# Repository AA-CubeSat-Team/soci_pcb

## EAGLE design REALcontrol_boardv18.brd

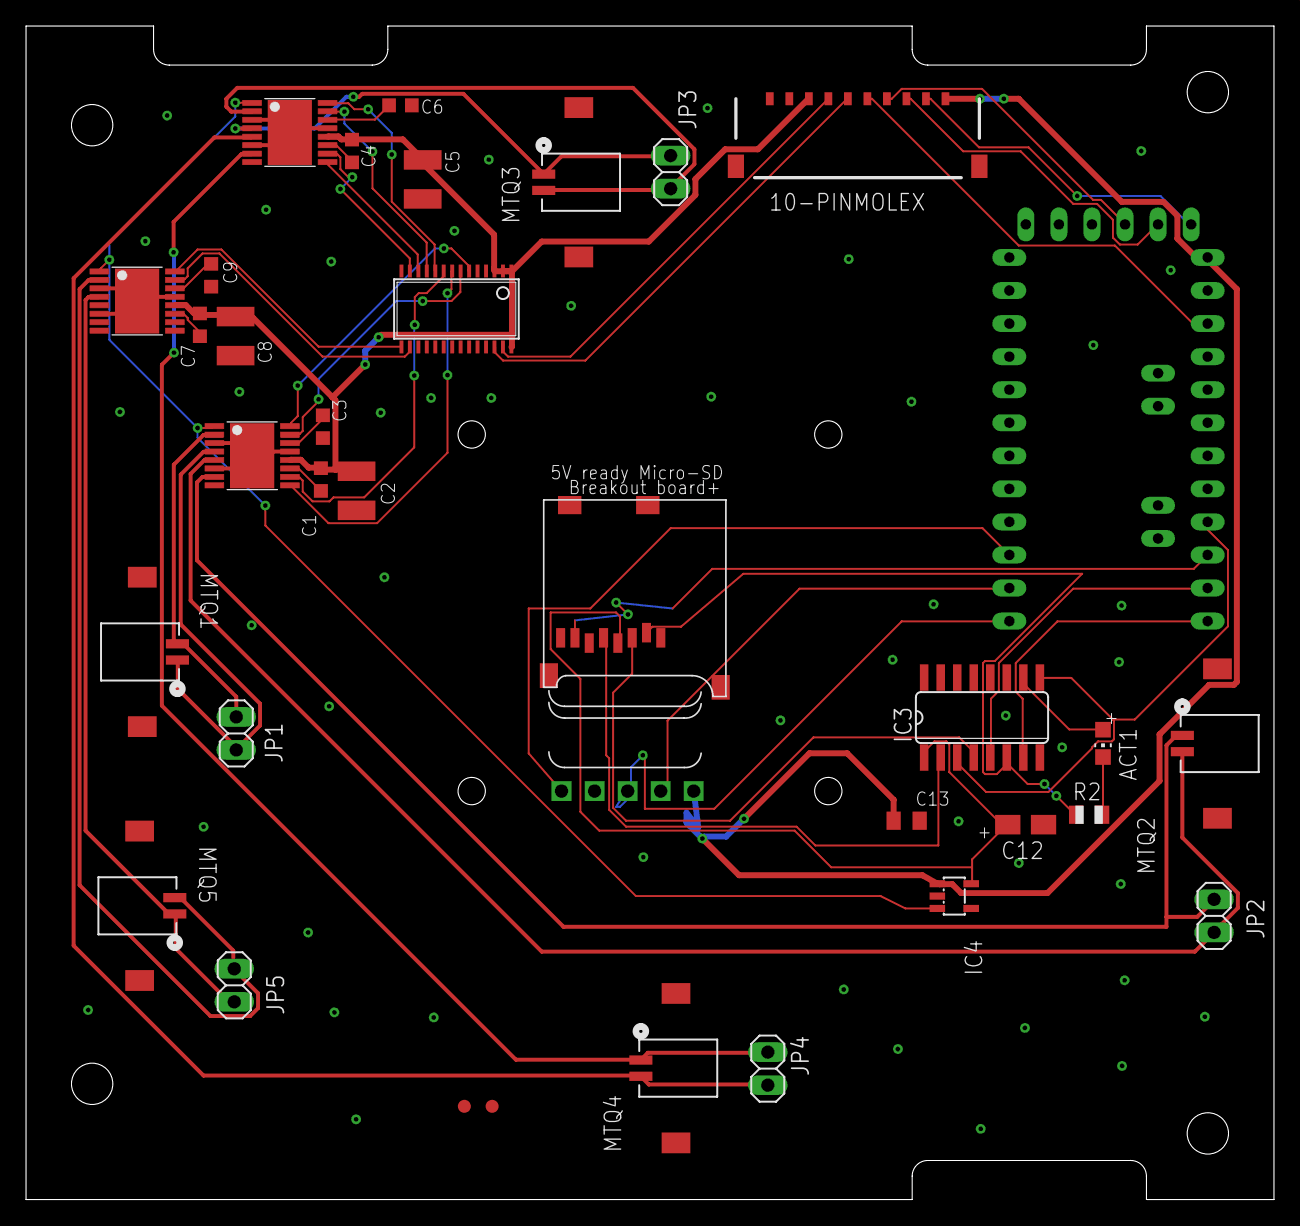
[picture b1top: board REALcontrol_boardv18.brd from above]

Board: 2 copper layers, 95.9 x 90.2 mm, 35 parts (0 on the bottom side), 49 nets.

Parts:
10-PINMOLEX: 504050-1091
ACT1: RED; CHIP-LED0805
C1, C4, C7: 0.01uF; C0603K
C2, C5, C8: 10uF; C1210K
C3, C6, C9: 2.2uF; C0603K
C12: 10uF/10V; A/3216-18R
C13: 0.1uF; C0805K
H-BRIDGE1, H-BRIDGE2, H-BRIDGE3: DRV8833PWP; HTSSOP16
IC3: 4050D; SO16
IC4: LP298XS; SOT23-5L
JP1, JP2, JP3, JP4, JP5: 1X02
MTQ1, MTQ2, MTQ3, MTQ4, MTQ5: DF13C-2P-1.25V(51); CON2_1X2_U_DF13
PWMDRIVER: PCA9685PW; TSSOP28
R2: 1K; R0805
U$2: UCAM-III
U$6, U$7: FIDUCIAL; FIDUCIAL_1MM
U$8: PRO-MINI-2
X2: MICROSD

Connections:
5V_1: 10-PINMOLEX.8, C1.1, C2.2, C4.1, C5.2, C7.1, C8.2, H-BRIDGE1.P12, H-BRIDGE2.P12, H-BRIDGE3.P12, PWMDRIVER.1, PWMDRIVER.2, PWMDRIVER.3, PWMDRIVER.28
5V_2: 10-PINMOLEX.1, C13.1, IC4.1, U$2.1, U$8.RAW
+3V3: C12.+, IC3.1, IC4.5, X2.4
CLK: IC3.3, IC3.9, U$8.D13
CS: IC3.7, U$8.D10
DI: IC3.5, U$8.D11
DO: U$8.D12, X2.7
GND: 10-PINMOLEX.9, C2.1, C3.1, C5.1, C6.1, C8.1, C9.1, C12.-, C13.2, H-BRIDGE1.P3, H-BRIDGE1.P6, H-BRIDGE1.P13, H-BRIDGE1.PAD, H-BRIDGE2.P3, H-BRIDGE2.P6, H-BRIDGE2.P13, H-BRIDGE2.PAD, H-BRIDGE3.P3, H-BRIDGE3.P6, H-BRIDGE3.P13, H-BRIDGE3.PAD, IC3.8, IC3.11, IC3.14, IC4.2, PWMDRIVER.4, PWMDRIVER.5, PWMDRIVER.14, PWMDRIVER.23, PWMDRIVER.24, PWMDRIVER.25, U$2.4, U$8.GND, U$8.GND1, U$8.GND2, U$8.GND3, X2.6, X2.MT1, X2.MT2
GRN: 10-PINMOLEX.2, U$8.DTR
MTQ1_A: H-BRIDGE1.P16, PWMDRIVER.6
MTQ1_B: H-BRIDGE1.P15, PWMDRIVER.7
MTQ2_A: H-BRIDGE1.P9, PWMDRIVER.8
MTQ2_B: H-BRIDGE1.P10, PWMDRIVER.9
MTQ3_A: H-BRIDGE2.P16, PWMDRIVER.10
MTQ3_B: H-BRIDGE2.P15, PWMDRIVER.11
MTQ4_A: H-BRIDGE2.P9, PWMDRIVER.12
MTQ4_B: H-BRIDGE2.P10, PWMDRIVER.13
MTQ5_A: H-BRIDGE3.P16, PWMDRIVER.15
MTQ5_B: H-BRIDGE3.P15, PWMDRIVER.16
unnamed: H-BRIDGE2.P2, JP3.2, MTQ3.2
unnamed: C3.2, H-BRIDGE1.P14
unnamed: H-BRIDGE1.P4, JP1.1, MTQ1.1
unnamed: H-BRIDGE1.P2, JP1.2, MTQ1.2
unnamed: H-BRIDGE1.P7, JP2.1, MTQ2.1
unnamed: H-BRIDGE1.P5, JP2.2, MTQ2.2
unnamed: C1.2, H-BRIDGE1.P11
unnamed: H-BRIDGE2.P7, JP4.1, MTQ4.1
unnamed: H-BRIDGE2.P5, JP4.2, MTQ4.2
unnamed: C6.2, H-BRIDGE2.P14
unnamed: C4.2, H-BRIDGE2.P11
unnamed: H-BRIDGE2.P4, JP3.1, MTQ3.1
unnamed: H-BRIDGE3.P2, JP5.2, MTQ5.2
unnamed: C9.2, H-BRIDGE3.P14
unnamed: C7.2, H-BRIDGE3.P11
unnamed: H-BRIDGE3.P4, JP5.1, MTQ5.1
unnamed: ACT1.A, IC3.10
unnamed: IC3.2, X2.5
unnamed: IC3.6, R2.1, X2.2
unnamed: ACT1.C, R2.2
unnamed: IC3.4, X2.3
unnamed: U$2.5, U$8.D7
RST: 10-PINMOLEX.5, U$8.RST
RX: U$2.3, U$8.D9
RXI: 10-PINMOLEX.4, U$8.RX1-1
SCL: 10-PINMOLEX.6, PWMDRIVER.26
SDA: 10-PINMOLEX.7, PWMDRIVER.27
TX: U$2.2, U$8.D8
TXO: 10-PINMOLEX.3, U$8.TX0-1
VCC: H-BRIDGE1.P1, H-BRIDGE2.P1, H-BRIDGE3.P1, IC4.3

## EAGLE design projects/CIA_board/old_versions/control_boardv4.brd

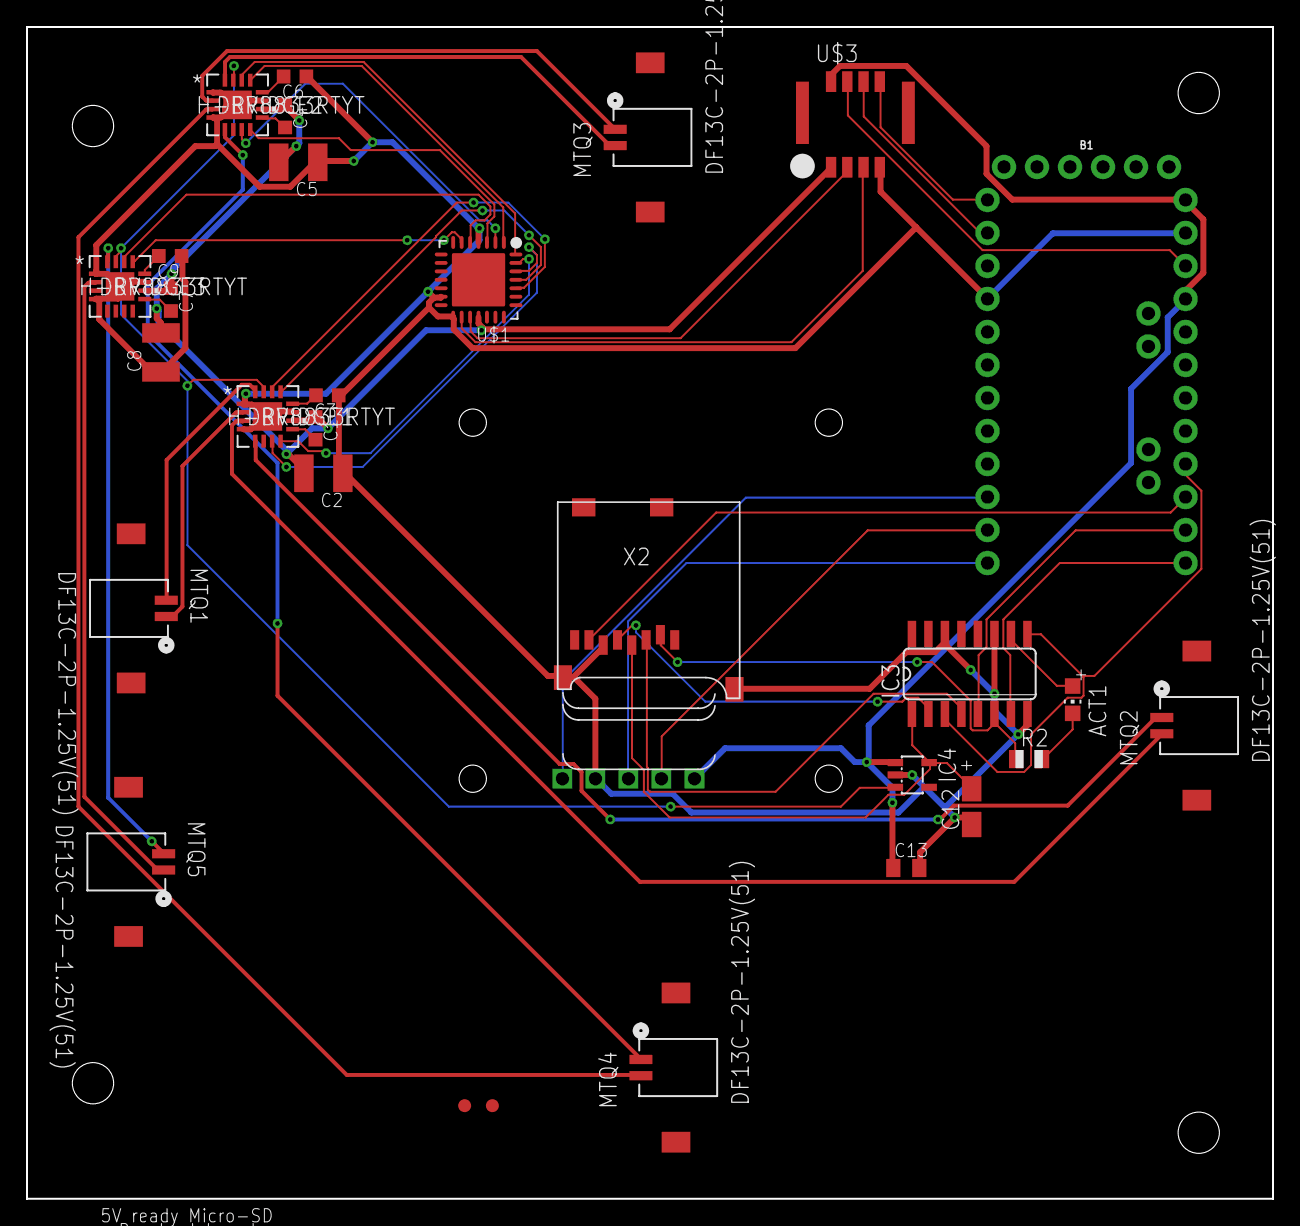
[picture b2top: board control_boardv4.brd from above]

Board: 2 copper layers, 95.9 x 90.2 mm, 30 parts (0 on the bottom side), 48 nets.

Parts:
ACT1: RED; CHIP-LED0805
B1: ARDUINO_PRO_MINI
C1, C4, C7: 0.01uF; C0603K
C2, C5, C8: 10uF; C1210K
C3, C6, C9: 2.2uF; C0603K
C12: 10uF/10V; A/3216-18R
C13: 0.1uF; C0805K
H-BRIDGE1, H-BRIDGE2, H-BRIDGE3: DRV8833RTYT; RTY16
IC3: 4050D; SO16
IC4: LP298XS; SOT23-5L
MTQ1, MTQ2, MTQ3, MTQ4, MTQ5: DF13C-2P-1.25V(51); CON2_1X2_U_DF13
R2: 1K; R0805
U$1: PCA9685BS; HVQFN28
U$2: UCAM-III
U$3: MOLEX_MICRO_LOCK_PLUS_8
U$6, U$7: FIDUCIAL; FIDUCIAL_1MM
X2: MICROSD

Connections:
5V_1: C1.1, C2.2, C4.1, C5.2, C7.1, C8.2, H-BRIDGE1.10, H-BRIDGE2.10, H-BRIDGE3.10, U$1.25, U$3.8
5V_2: B1.21, B1.24, C13.1, IC4.1, U$2.1, U$3.1
+3V3: C12.+, IC3.1, IC4.5, X2.4
CLK: B1.16, IC3.3, IC3.9
CS: B1.13, IC3.7
DI: B1.14, IC3.5
DO: B1.15, X2.7
GND: B1.4, B1.23, C2.1, C3.1, C5.1, C6.1, C8.1, C9.1, C12.-, C13.2, H-BRIDGE1.1, H-BRIDGE1.4, H-BRIDGE1.11, H-BRIDGE1.17, H-BRIDGE2.1, H-BRIDGE2.4, H-BRIDGE2.11, H-BRIDGE2.17, H-BRIDGE3.1, H-BRIDGE3.4, H-BRIDGE3.11, H-BRIDGE3.17, IC3.8, IC3.11, IC3.14, IC4.2, U$1.11, U$1.20, U$1.22, U$2.4, U$3.5, X2.6, X2.MT1, X2.MT2
MTQ1_A: H-BRIDGE1.14, U$1.3
MTQ1_B: H-BRIDGE1.13, U$1.4
MTQ2_A: H-BRIDGE1.7, U$1.5
MTQ2_B: H-BRIDGE1.8, U$1.6
MTQ3_A: H-BRIDGE2.14, U$1.7
MTQ3_B: H-BRIDGE2.13, U$1.8
MTQ4_A: H-BRIDGE2.7, U$1.9
MTQ4_B: H-BRIDGE2.8, U$1.10
MTQ5_A: H-BRIDGE3.14, U$1.12
MTQ5_B: H-BRIDGE3.13, U$1.13
unnamed: H-BRIDGE2.16, MTQ3.2
unnamed: C3.2, H-BRIDGE1.12
unnamed: H-BRIDGE1.2, MTQ1.1
unnamed: H-BRIDGE1.16, MTQ1.2
unnamed: H-BRIDGE1.5, MTQ2.1
unnamed: H-BRIDGE1.3, MTQ2.2
unnamed: C1.2, H-BRIDGE1.9
unnamed: H-BRIDGE2.5, MTQ4.1
unnamed: H-BRIDGE2.3, MTQ4.2
unnamed: C6.2, H-BRIDGE2.12
unnamed: C4.2, H-BRIDGE2.9
unnamed: H-BRIDGE2.2, MTQ3.1
unnamed: H-BRIDGE3.16, MTQ5.2
unnamed: C9.2, H-BRIDGE3.12
unnamed: C7.2, H-BRIDGE3.9
unnamed: H-BRIDGE3.2, MTQ5.1
unnamed: ACT1.A, IC3.10
unnamed: IC3.2, X2.5
unnamed: IC3.6, R2.1, X2.2
unnamed: ACT1.C, R2.2
unnamed: IC3.4, X2.3
unnamed: B1.10, U$2.5
RST: B1.22, U$3.2
RX: B1.12, U$2.3
RXI: B1.2, U$3.3
SCL: U$1.23, U$3.6
SDA: U$1.24, U$3.7
TX: B1.11, U$2.2
TXO: B1.1, U$3.4
VCC: H-BRIDGE1.15, H-BRIDGE2.15, H-BRIDGE3.15, IC4.3

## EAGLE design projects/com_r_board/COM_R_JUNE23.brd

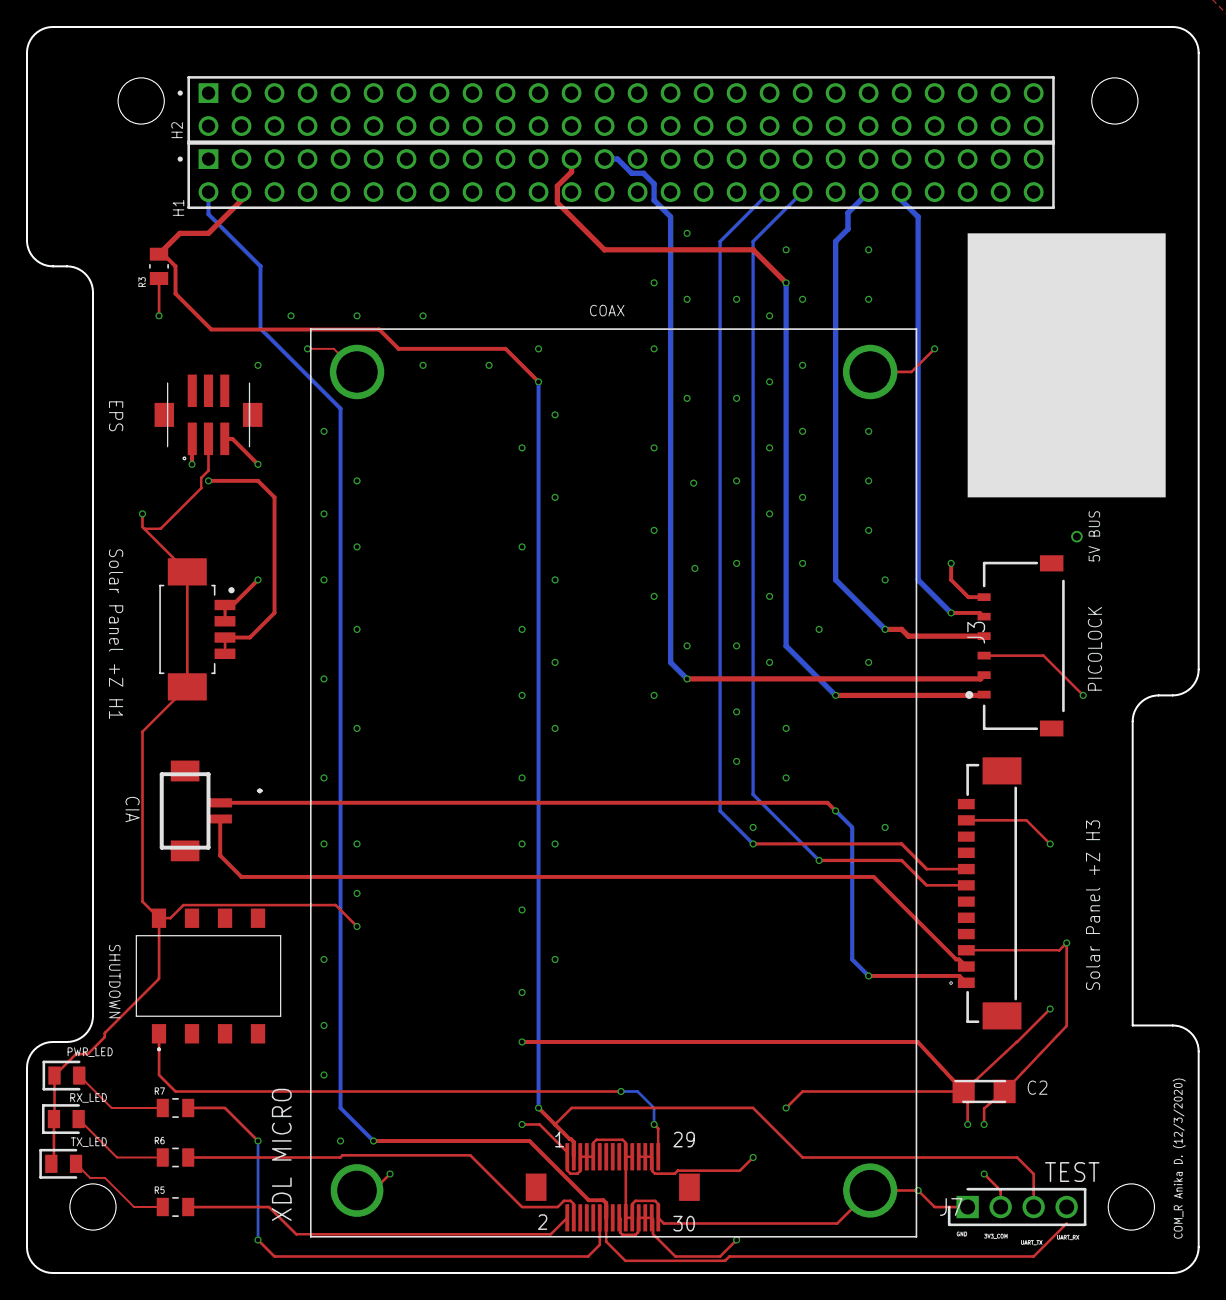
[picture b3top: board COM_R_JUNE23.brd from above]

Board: 4 copper layers, 90.2 x 95.9 mm, 18 parts (0 on the bottom side), 22 nets.

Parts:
C2: 293D106X0010A2TE3; CAPPM3216X180N
J1: 0532610471; MOLEX_0532610471
J2: 53398-1271
J3: 504050-0691; 504050-0691_2
J4, J5: ESQ-126-39-G-D; SAMTEC_ESQ-126-39-G-D
J6: G125-MS10605L3P
J7: 61300411121; HDRV4W95P0X254_1X4_1016X254X85
PWR_LED: HSMQ-C170-T0000; LEDC2012X90N
R3: TNPW080510K0BETY; RESC2012X55N
R5, R6, R7: Y40621K00000Q0R; RESC2012X64N
RX_LED: HSMQ-C170-T0000; LEDC2012X90N
S1: A6S-4104-H; A6S4104H
TX_LED: HSMQ-C170-T0000; LEDC2012X90N
U$1: DF13-2P-1.25V; DF13C-2P-1.25V
U$3: KYOCERA_5046_30PIN

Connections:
3V3_COM: C2.1, J2.11, J5.17, J7.2, U$3.P$18, U$3.P$23, U$3.P$24, U$3.P$25, U$3.P$26, U$3.P$27, U$3.P$28
5V_BUS: J3.6, J5.25
ANT_BURN1: J3.1, J4.23
ANT_BURN2: J3.2, J4.25
GND: C2.2, J1.S1, J1.S2, J2.3, J3.3, J5.10, J5.13, J5.18, J5.21, J5.22, J5.29, J5.30, J5.31, J5.47, J5.48, J5.51, J6.2, J7.1, PWR_LED.1, R3.1, RX_LED.1, S1.8, TX_LED.1, U$3.P$1, U$3.P$5, U$3.P$7, U$3.P$9, U$3.P$19, U$3.P$20, U$3.P$21, U$3.P$22, U$3.P$30, U$3.P$33, U$3.P$34, U$3.P$35, U$3.P$36
I2C1_SCL: J3.5, J4.44
I2C1_SDA: J3.4, J4.42
unnamed: R5.1, TX_LED.2
unnamed: PWR_LED.2, R7.1
unnamed: R6.1, RX_LED.2
NEG_LEAD: J2.2, U$1.P$2
PH5_NEG: J2.7, J4.38
PH5_POS: J2.8, J4.36
POS_LEAD: J2.1, U$1.P$1
PWR_LED: R7.2, U$3.P$12
RX_LED: R6.2, U$3.P$4
SA_PWR: J1.3, J1.4, J6.1
SA_RTN: J1.1, J1.2, J6.3
SHUTDOWN: S1.1, U$3.P$29
TX_LED: R5.2, U$3.P$2
UART1_RX: J4.02, J7.4, U$3.P$14
UART1_TX: J4.04, J7.3, R3.2, U$3.P$3

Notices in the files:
parts and their libraries:
SparkFun-Boards: Licensing: Creative Commons ShareAlike 4.0 International - https://creativecommons.org/licenses/by-sa/4.0
